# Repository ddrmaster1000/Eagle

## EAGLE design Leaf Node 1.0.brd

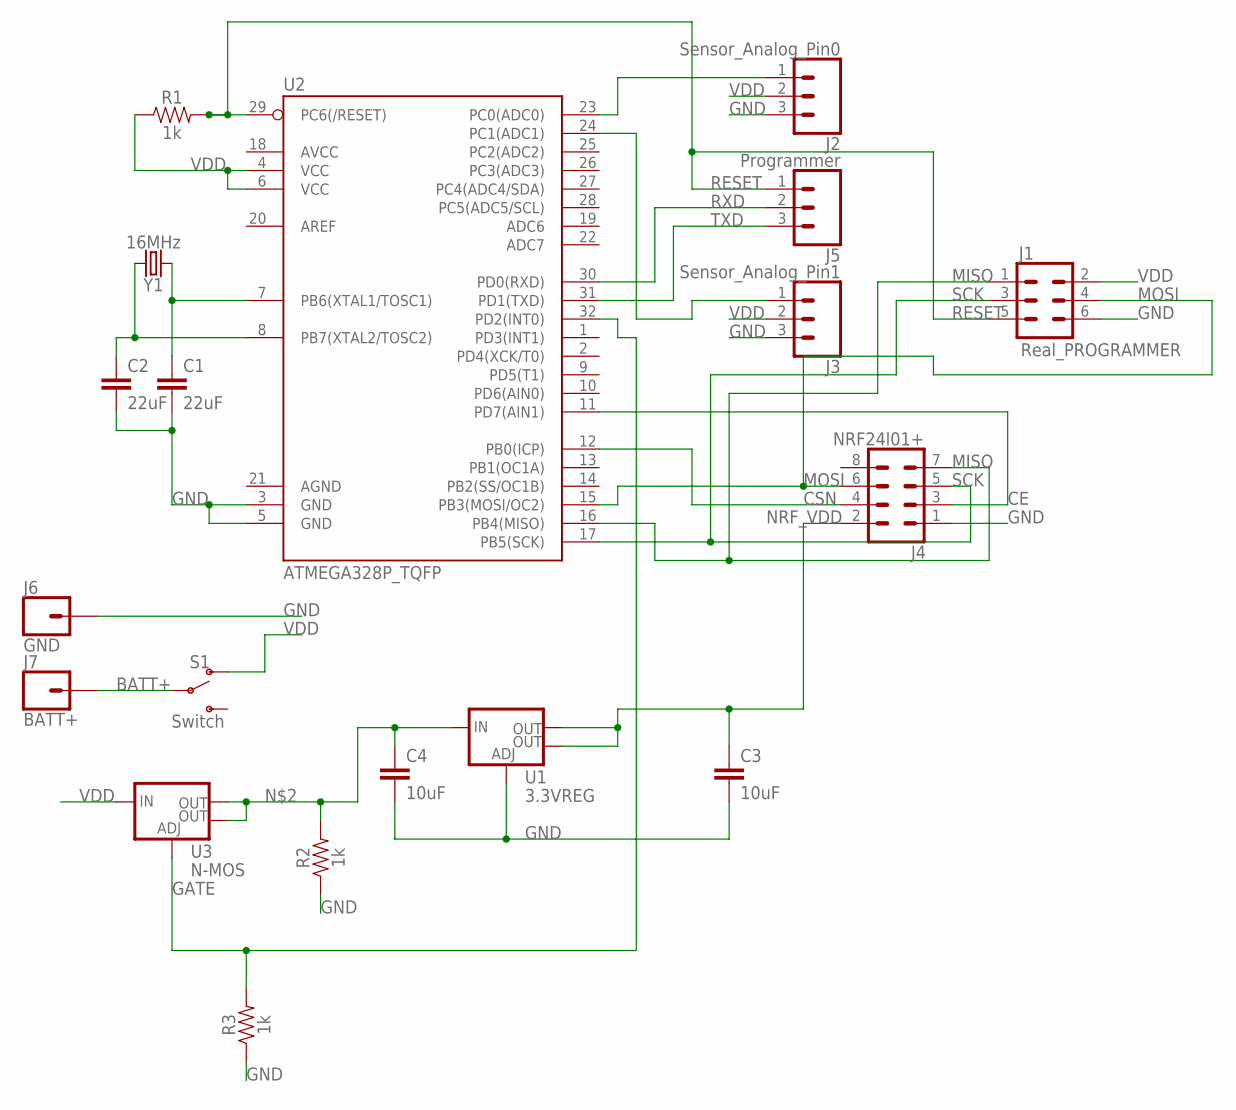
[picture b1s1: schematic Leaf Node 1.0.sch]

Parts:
C1, C2: 22uF; 0805
C3, C4: 10uF; 0805
J1: Real_PROGRAMMER; 2X3
J2: Sensor_Analog_Pin0; 1X03
J3: Sensor_Analog_Pin1; 1X03
J4: NRF24l01+; 2X4
J5: Programmer; 1X03
J6: GND; 1X01
J7: BATT+; 1X01
R1, R2, R3: 1k; 0805
S1: Switch; SWITCH_SPDT_PTH_11.6X4.0MM
U1: 3.3VREG; SOT223
U2: ATMEGA328P_TQFP; TQFP32-08
U3: N-MOS; SOT223
Y1: 16MHz; HC49US

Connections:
BATT+: J7.1, S1.2
CE: J4.3, U2.11 (PD7(AIN1))
CSN: J4.4, U2.12 (PB0(ICP))
GATE: R3.2, U2.32 (PD2(INT0)), U3.1 (ADJ)
GND: C1.2, C2.2, C3.2, C4.2, J1.6, J2.3, J3.3, J4.1, J6.1, R2.1, R3.1, U1.1 (ADJ), U2.3 (GND), U2.5 (GND)
MISO: J1.1, J4.7, U2.16 (PB4(MISO))
MOSI: J1.4, J4.6, U2.15 (PB3(MOSI/OC2))
unnamed: C2.1, U2.8 (PB7(XTAL2/TOSC2)), Y1.2
unnamed: C4.1, R2.2, U1.3 (IN), U3.2 (OUT), U3.4 (OUT)
unnamed: C1.1, U2.7 (PB6(XTAL1/TOSC1)), Y1.1
unnamed: J3.1, U2.24 (PC1(ADC1))
unnamed: J2.1, U2.23 (PC0(ADC0))
NRF_VDD: C3.1, J4.2, U1.2 (OUT), U1.4 (OUT)
RESET: J1.5, J5.1, R1.2, U2.29 (PC6(/RESET))
RXD: J5.2, U2.30 (PD0(RXD))
SCK: J1.3, J4.5, U2.17 (PB5(SCK))
TXD: J5.3, U2.31 (PD1(TXD))
VDD: J1.2, J2.2, J3.2, R1.1, S1.1 (O), U2.4 (VCC), U2.6 (VCC), U3.3 (IN)

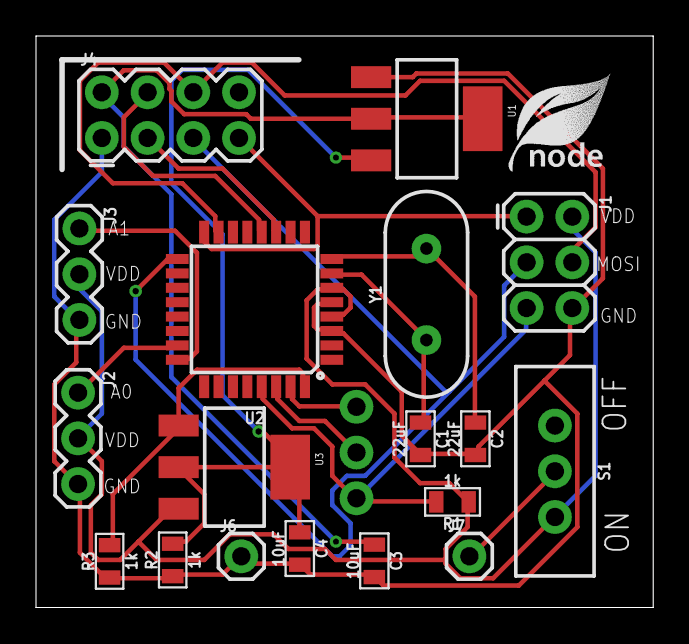
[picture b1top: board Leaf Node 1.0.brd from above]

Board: 2 copper layers, 34.3 x 31.8 mm, 19 parts (1 on the bottom side), 18 nets.

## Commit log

2018-09-13 Leaf Node

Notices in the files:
parts and their libraries:
SparkFun-Capacitors: Licensing: Creative Commons ShareAlike 4.0 International - https://creativecommons.org/licenses/by-sa/4.0
